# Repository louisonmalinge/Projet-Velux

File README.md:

Bonjour et bienvenue sur le Git qui a permis de réaliser le projet d’automatisation du banc de test de panneau solaire. Vous retrouverez dans ce Git tous les fichiers qui ont contribué à la réalisation du projet.

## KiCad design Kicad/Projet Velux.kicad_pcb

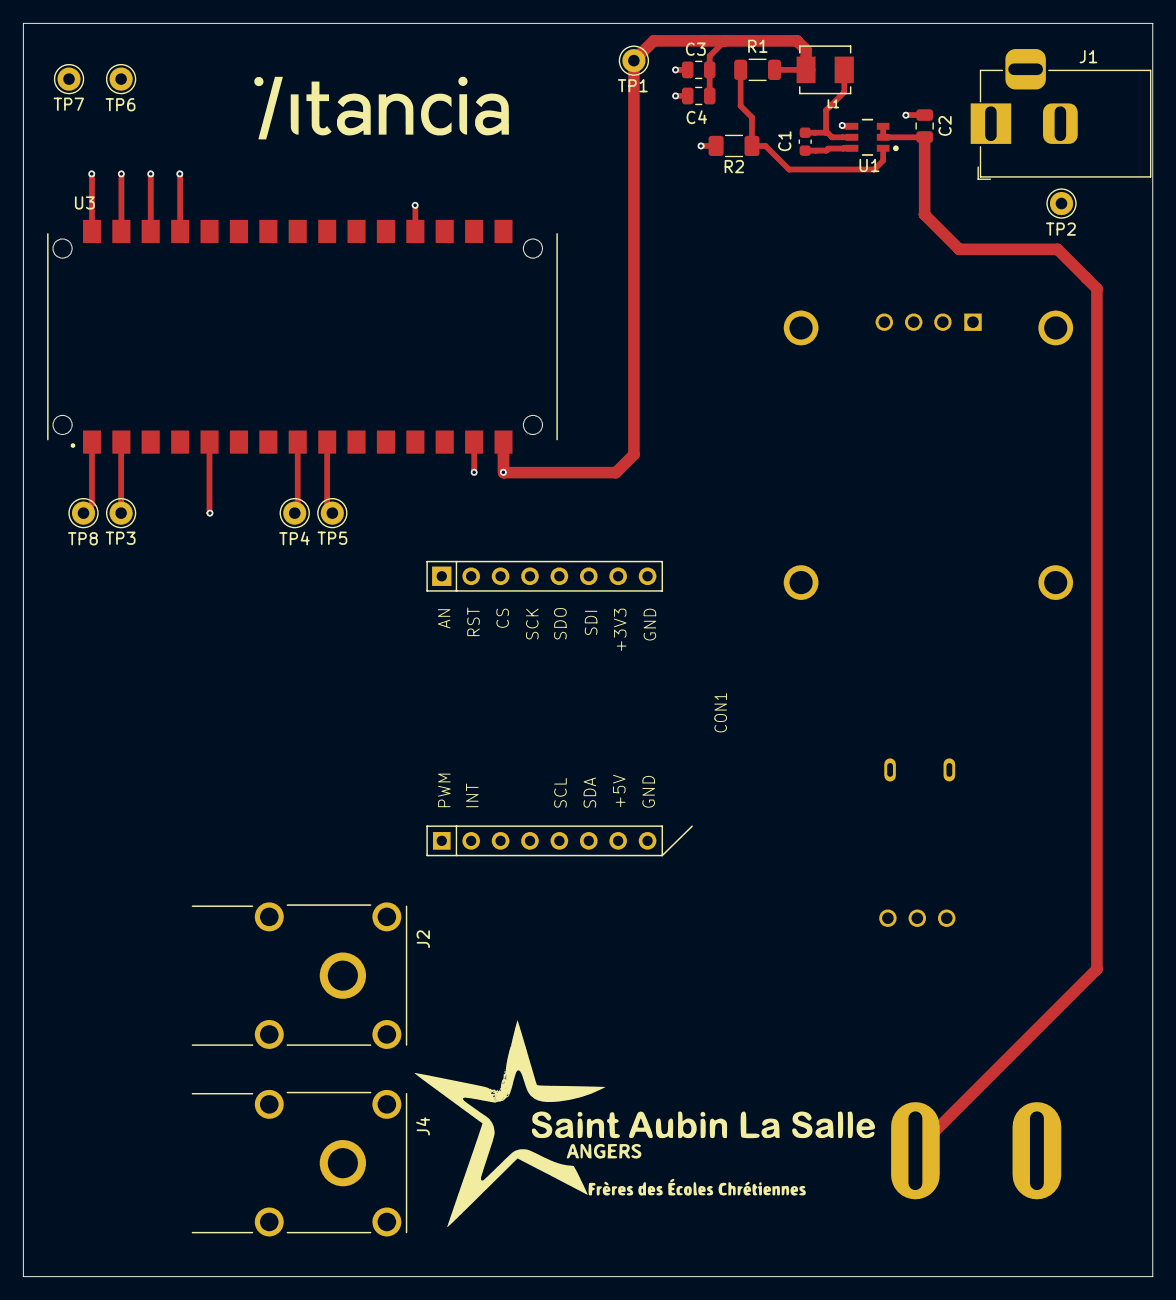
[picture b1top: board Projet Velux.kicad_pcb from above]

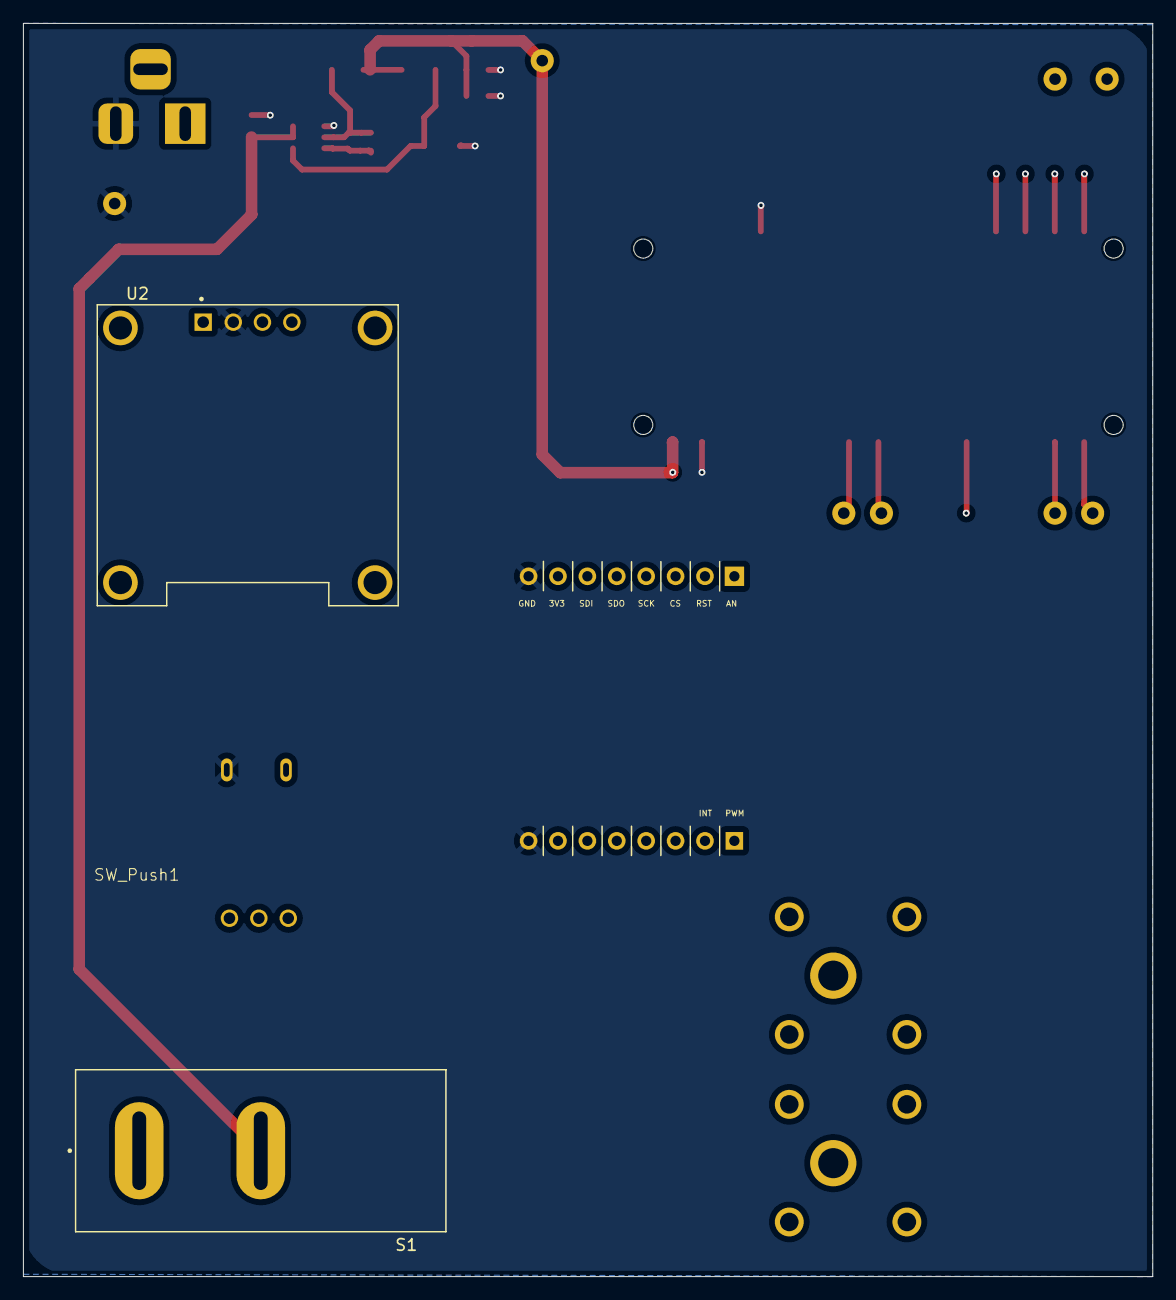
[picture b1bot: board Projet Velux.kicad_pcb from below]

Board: 4 copper layers, 97.6 x 108.3 mm, 25 parts (5 on the bottom side), 18 nets.

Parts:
C1: 0.1µF; C_0603_1608Metric
C2: 2.2µF; C_0805_2012Metric
C3, C4: 22µF; C_0805_2012Metric
CON1: MIKROBUS_MODULE_CONN
J1: Connecteur Alimentation; BarrelJack_Horizontal
J2: FCR7350R; FCR7350
J3: Connecteur Panneau Solaire; Connecteur panneau solaire
J4: FCR7350B; FCR7350
L1: 4.7µH; IND_SPM4020T-4R7M-LR
R1: 53.6k; R_1206_3216Metric
R2: 10.2k; R_1206_3216Metric_Pad1.30x1.75mm_HandSolder
S1: RB141C1100; SW_RB141C1100
SW_Push1: SW_Push; Bouton poussoir
TP1, TP2, TP3, TP4, TP5, TP6, TP7, TP8: TestPoint; Pin_D1.0mm_L10.0mm
U1: LMR51625YFDDCR; DDC0006A-MFG
U2: DM-OLED096-636; MODULE_DM-OLED096-636
U3: ABX00027; MODULE_ABX00027

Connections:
+3.3V: CON1.P7 (3V3), TP3.1, U2.2 (VCC_IN), U3.2 (+3V3)
+5V: C3.1, C4.1, L1.2, R1.1, TP1.1, U3.15 (VIN)
+24V: J1.1, S1.1
/A1: SW_Push1.2, U3.5 (A1)
/CS: CON1.P3 (CS), U3.28 (D10/PWM)
/MISO: CON1.P5 (MISO), TP7.1, U3.30 (D12/MISO)
/MOSI: CON1.P6 (MOSI), TP6.1, U3.29 (D11/MOSI)
/RST: CON1.P2 (RST), U3.27 (D9/PWM)
/SCK: CON1.P4 (SCK), TP8.1, U3.1 (D13)
/SCL: TP5.1, U2.3 (SCL), U3.9 (A5/SCL)
/SDA: TP4.1, U2.4 (SDA), U3.8 (A4/SDA)
/switch: C2.1, S1.2, U1.2 (EN), U1.3 (VIN)
GND: C2.2, C3.2, C4.2, CON1.P8 (GND1), CON1.P9 (GND2), J1.2, R2.2, SW_Push1.1, TP2.1, U1.4 (GND), U2.1 (GND), U3.14 (GND), U3.19 (GND)
unnamed: J2.P$1, J2.P$2, J2.P$3, J2.P$4, J2.P$5, J3.1
unnamed: J3.3, J4.P$1, J4.P$2, J4.P$3, J4.P$4, J4.P$5
unnamed: C1.1, U1.6 (CB)
unnamed: R1.2, R2.1, U1.1 (FB)
unnamed: C1.2, L1.1, U1.5 (SW)

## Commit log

2026-03-29 Kicad
2026-03-29 Create test
2026-04-22 Add main Arduino program for Velux project
2026-04-22 Add Ecran.h header file for OLED display functions
2026-04-22 Add Siglent.h header file with function declarations
2026-04-22 Add Siglent communication and measurement functions
    This file contains functions for measuring voltage, current, and power using Ethernet communication with Siglent instruments.
2026-04-22 Add Ecran.h for OLED display functionality
2026-04-22 Add Ecran.cpp for display management functions
2026-04-22 Add Siglent.h header file for Ethernet functions
2026-04-22 Add Siglent communication functions for Arduino
2026-04-23 Update readme with code functionality details
    Added explanations for the code's functionality and purpose.
2026-04-23 Add readme with project description and features
    Initial readme file with project overview and functionality.
2026-04-23 Update Readme with project details
    Added description of fill factor calculation and connection test.
2026-04-23 Update readme to include new button management files
    Added Bouton.h and Bouton.cpp to manage button value across multiple files.
2026-04-23 Add initial Arduino sketch for project
2026-04-23 Add Ecran.cpp for OLED display management
    This file contains functions for initializing and displaying messages on an OLED screen, handling button inputs, and performing tests related to solar panel and multimeter connections.
2026-04-23 Add Siglent.h header file for Ethernet communication
2026-04-23 Add Siglent communication functions for measurements
2026-04-23 Add header file for button initialization and state handling
2026-04-23 Add button handling functionality in Bouton.cpp
2026-04-24 Initialize Arduino project with display and button handling
2026-04-24 Add Ecran.cpp for display management in solar tests
    This file contains functions to initialize and manage the display for solar panel testing, including setup, displaying messages, and testing connections with solar panels, chargers, and multimeters.
2026-04-24 Clean up Siglent.h by removing excess whitespace
    Remove unnecessary whitespace and comments in Siglent.h
2026-04-24 Add header file for button initialization and state
2026-04-24 Add button state reading functionality
2026-05-19 Refactor display functions and variable declarations
2026-05-19 Refactor Siglent.cpp for improved clarity and structure
2026-05-19 Mise à jour du readme avec les résultats des tests
    Ajout d'une fonction pour compter les panneaux solaires positifs et négatifs.
2026-05-19 Update readme with new solar panel testing options
    Added functionality to check if the solar panel is connected.
2026-05-21 Create Plan_de_test_V2
